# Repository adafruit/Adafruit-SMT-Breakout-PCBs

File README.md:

## Adafruit SMT Breakout PCBs
<a href="http://www.adafruit.com/products/1377"><br/>
Click here to purchase one from the Adafruit shop</a>

Beguiled by a fancy new chip that is only available in a strange pinout? These breakout PCBs will make your life much much easier and get you prototyping faster than ever.

All the basic SMT breakouts are here!

For more details, check out the product pages at

  * https://www.adafruit.com/products/1377 (48-pin)
  * https://www.adafruit.com/products/1162 (44-pin)
  * https://www.adafruit.com/products/1163 (32-pin)
  * https://www.adafruit.com/products/1208 (28-pin)
  * https://www.adafruit.com/products/1206 (20-pin)
  * https://www.adafruit.com/products/1207 (16-pin)
  * https://www.adafruit.com/products/1210 (14-pin)
  * https://www.adafruit.com/products/1211 (12-pin)
  * https://www.adafruit.com/products/1212 (8-pin)
  * https://www.adafruit.com/products/1230 (SOT & TO252 set)
  * https://www.adafruit.com/product/1762 (5050 LED)
  * https://www.adafruit.com/product/1863 (JST 2-PH w/switch)
  * https://www.adafruit.com/products/1862 (JST 2-PH)
  * https://www.adafruit.com/products/1868 (12mm coin)
  * https://www.adafruit.com/products/1867 (12mm coin w/switch)
  * https://www.adafruit.com/products/1870 (20mm coin)
  * https://www.adafruit.com/products/1871 (20mm coin w/switch)
  * https://www.adafruit.com/products/1833 (micro B)
  * https://www.adafruit.com/products/1764 (mini B)
  * https://www.adafruit.com/product/4984 (DVI)
  
PCB files for Adafruit SMT Basic Breakouts. The format is EagleCAD schematic and board layout

### License

Adafruit invests time and resources providing this open source design, please support Adafruit and open-source hardware by purchasing products from [Adafruit](https://www.adafruit.com)!

All text above must be included in any redistribution

Designed by Limor Fried/Ladyada for Adafruit Industries.
Creative Commons Attribution/Share-Alike, all text above must be included in any redistribution. 
See license.txt for additional information.

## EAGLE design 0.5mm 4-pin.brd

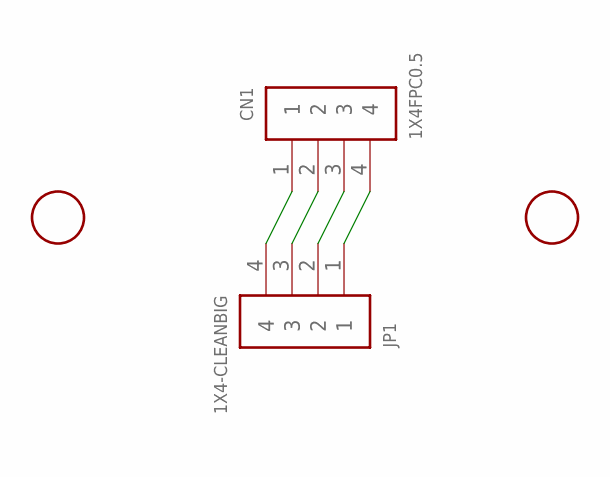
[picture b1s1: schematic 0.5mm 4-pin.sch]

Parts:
CN1: 1X4FPC0.5; FPC_0.5MM-4
JP1: 1X4-CLEANBIG; 1X04-CLEANBIG
U$2, U$3: FIDUCIAL; FIDUCIAL_1MM

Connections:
unnamed: CN1.4, JP1.1
unnamed: CN1.3, JP1.2
unnamed: CN1.2, JP1.3
unnamed: CN1.1, JP1.4

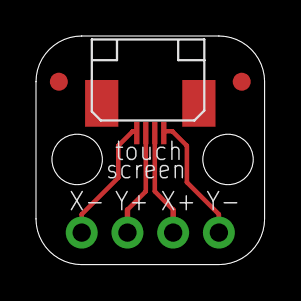
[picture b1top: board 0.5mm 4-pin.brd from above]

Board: 2 copper layers, 12.7 x 12.7 mm, 5 parts (1 on the bottom side), 4 nets.

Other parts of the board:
U$1: ADAFRUIT200MIL

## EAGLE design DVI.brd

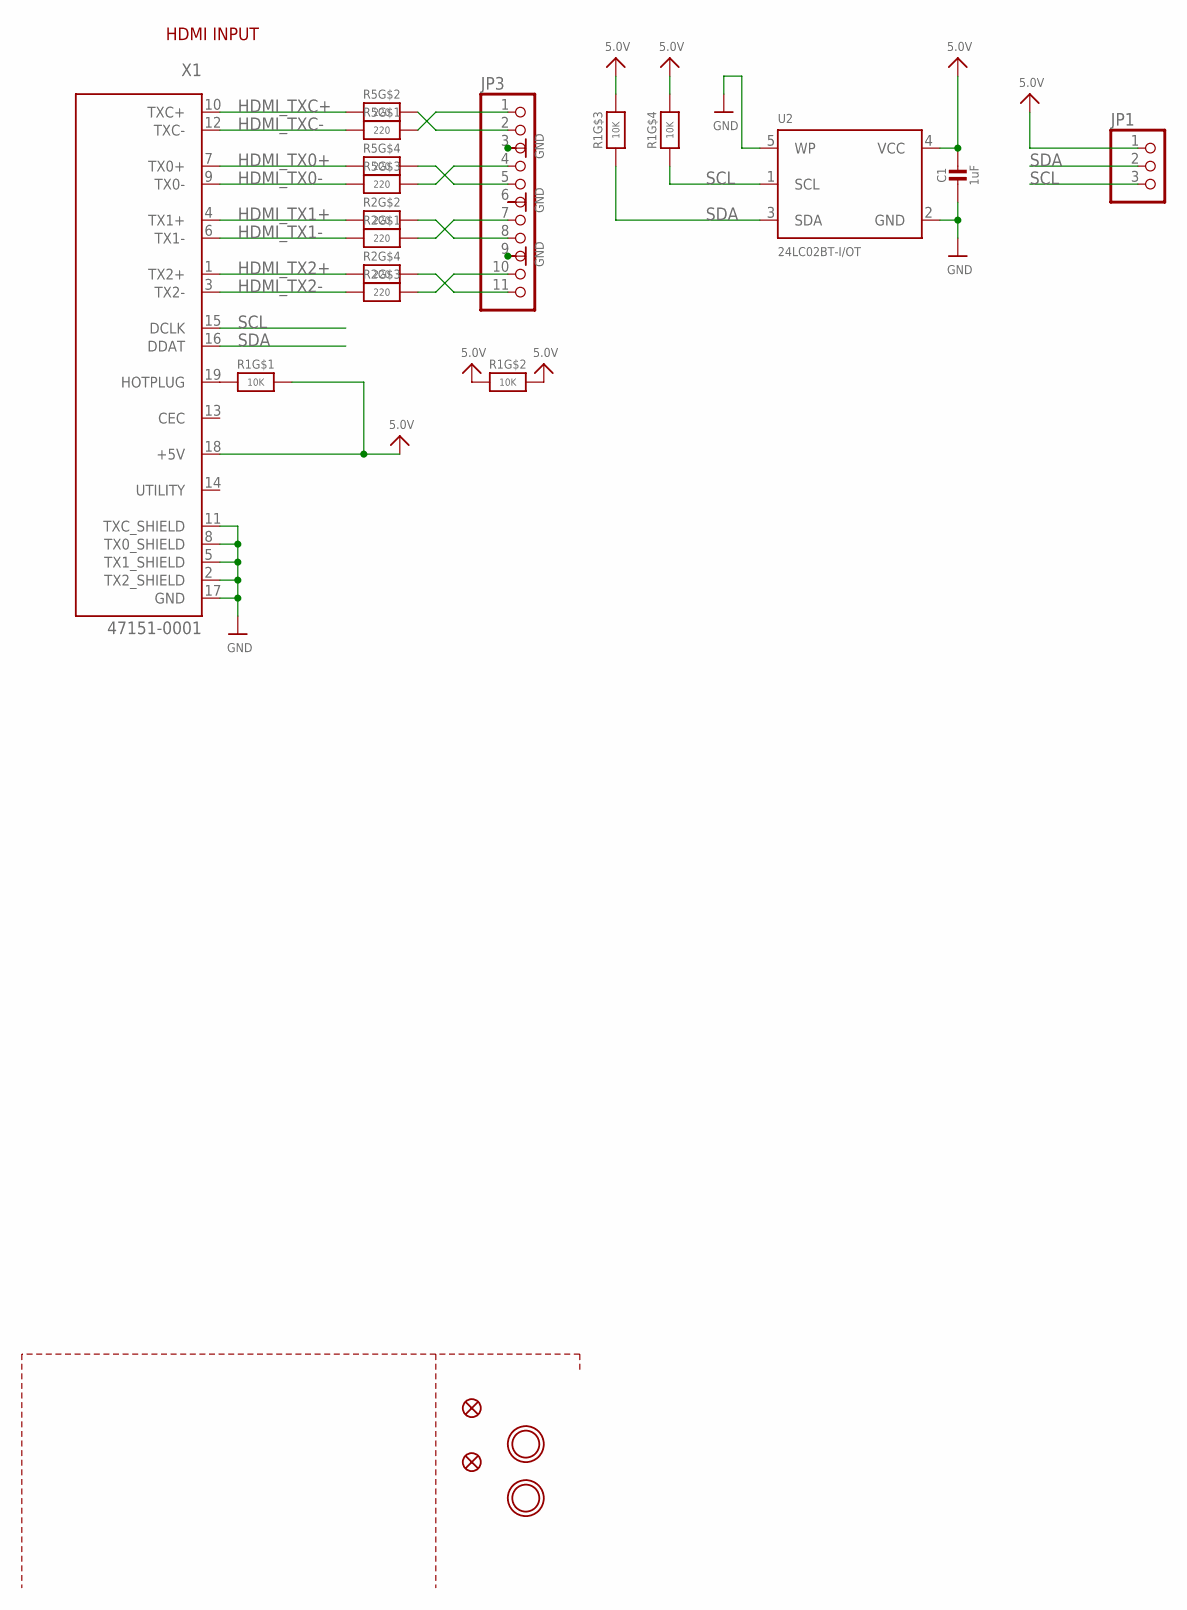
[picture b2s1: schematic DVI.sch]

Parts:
C1: 1uF; 0603-NO
FID1, FID2: FIDUCIAL_1MM
JP1: HEADER-1X3ROUND; 1X03_ROUND
JP3: HEADER-1X11; 1X11_ROUND
R1: 10K; RESPACK_4X0603
R2, R5: 220; RESPACK_4X0603
U2: 24LC02BT-I/OT; SOT23-5
U$32, U$33: MOUNTINGHOLE2.5; MOUNTINGHOLE_2.5_PLATED
X1: 47151-0001; HDMI_MOLEX_47151-0001

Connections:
5.0V: C1.1, JP1.1, R1.2 (1), R1.5 (2), R1.6 (2), R1.7 (2), R1.8 (2), U2.4 (VCC), X1.18 (+5V)
GND: C1.2, JP3.3, JP3.6, JP3.9, U2.2 (GND), U2.5 (WP), X1.2 (TX2_SHIELD), X1.5 (TX1_SHIELD), X1.8 (TX0_SHIELD), X1.11 (TXC_SHIELD), X1.17 (GND), X1.P$1 (GND), X1.P$2 (GND), X1.P$3 (GND), X1.P$4 (GND)
HDMI_TX0+: R5.4 (1), X1.7 (TX0+)
HDMI_TX0-: R5.3 (1), X1.9 (TX0-)
HDMI_TX1+: R2.2 (1), X1.4 (TX1+)
HDMI_TX1-: R2.1, X1.6 (TX1-)
HDMI_TX2+: R2.4 (1), X1.1 (TX2+)
HDMI_TX2-: R2.3 (1), X1.3 (TX2-)
HDMI_TXC+: R5.2 (1), X1.10 (TXC+)
HDMI_TXC-: R5.1, X1.12 (TXC-)
unnamed: R1.1, X1.19 (HOTPLUG)
SCL: JP1.3, R1.4 (1), U2.1 (SCL), X1.15 (DCLK)
SDA: JP1.2, R1.3 (1), U2.3 (SDA), X1.16 (DDAT)
TX0+: JP3.5, R5.5 (2)
TX0-: JP3.4, R5.6 (2)
TX1+: JP3.8, R2.7 (2)
TX1-: JP3.7, R2.8 (2)
TX2+: JP3.11, R2.5 (2)
TX2-: JP3.10, R2.6 (2)
TXC+: JP3.2, R5.7 (2)
TXC-: JP3.1, R5.8 (2)

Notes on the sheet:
HDMI INPUT

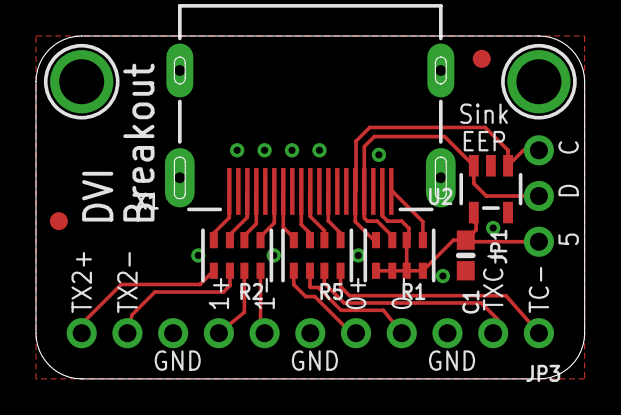
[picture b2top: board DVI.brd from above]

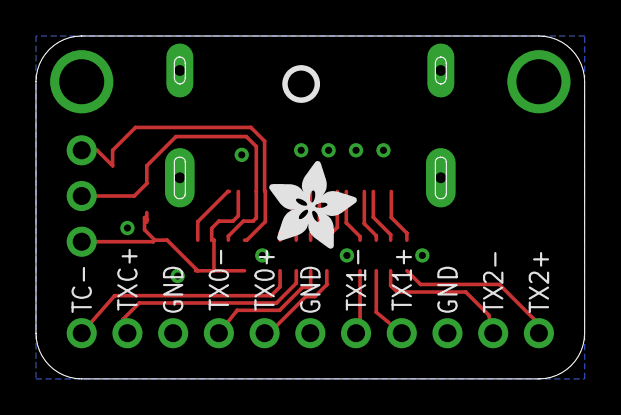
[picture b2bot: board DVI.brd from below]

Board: 2 copper layers, 30.5 x 19.1 mm, 14 parts (2 on the bottom side), 21 nets.

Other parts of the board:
U$6: ADAFRUIT_5MM
U$73: PCBFEAT-REV-040

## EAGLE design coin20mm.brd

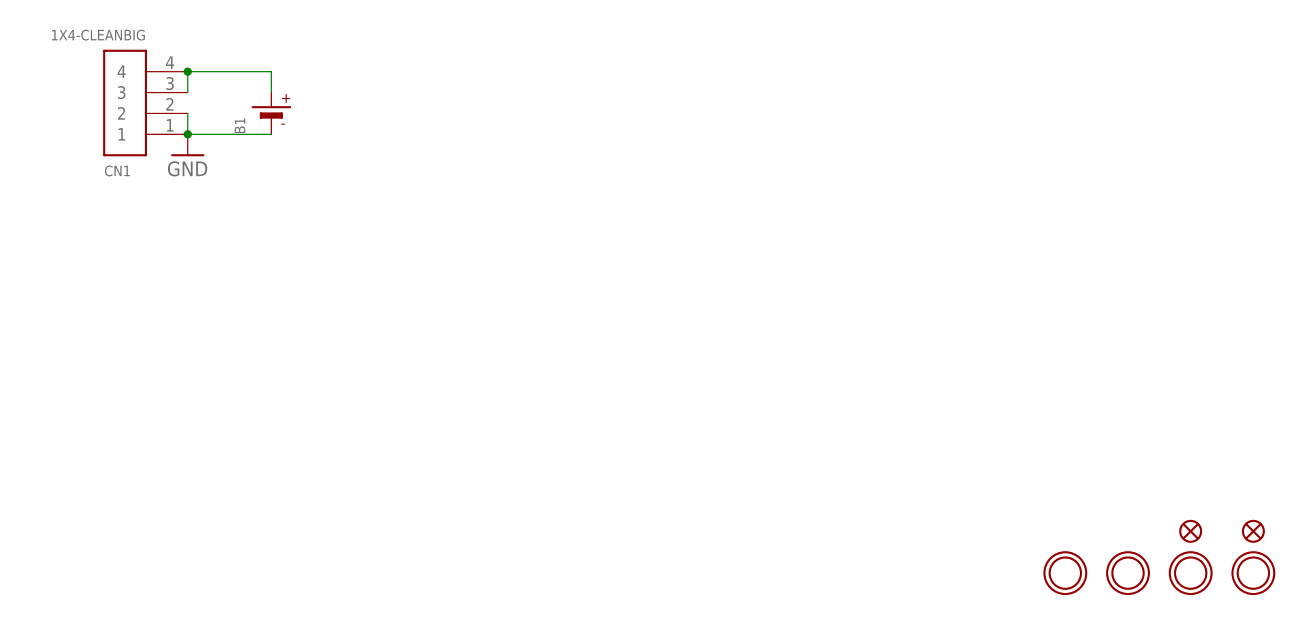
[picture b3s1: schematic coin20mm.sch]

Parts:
B1: BATTERYCR2032_BAT-HLD-001; CR2032_SMT_BAT-HLD-001
CN1: 1X4-CLEANBIG; 1X04-CLEANBIG
FID1, FID2: FIDUCIAL""; FIDUCIAL_1MM
U$1, U$2, U$3, U$5: MOUNTINGHOLE2.5; MOUNTINGHOLE_2.5_PLATED

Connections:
3V: B1.+$1 (+), B1.+$2 (+), CN1.3, CN1.4
GND: B1.-, CN1.1, CN1.2

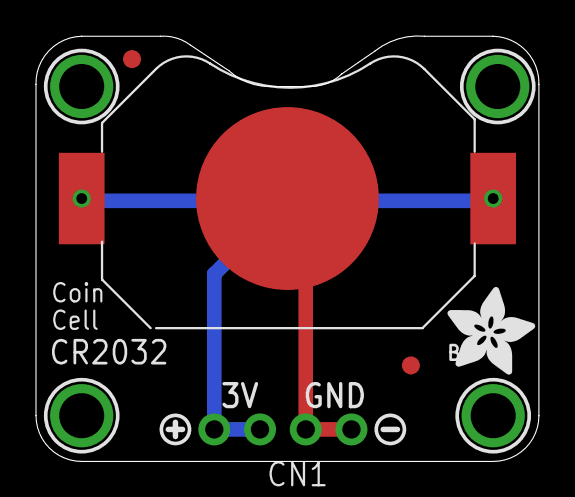
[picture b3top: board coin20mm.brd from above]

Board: 2 copper layers, 27.9 x 23.6 mm, 11 parts (0 on the bottom side), 2 nets.

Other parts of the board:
U$4: ADAFRUIT_5MM
U$6: SYMBOL_PLUS
U$7: SYMBOL_MINUS

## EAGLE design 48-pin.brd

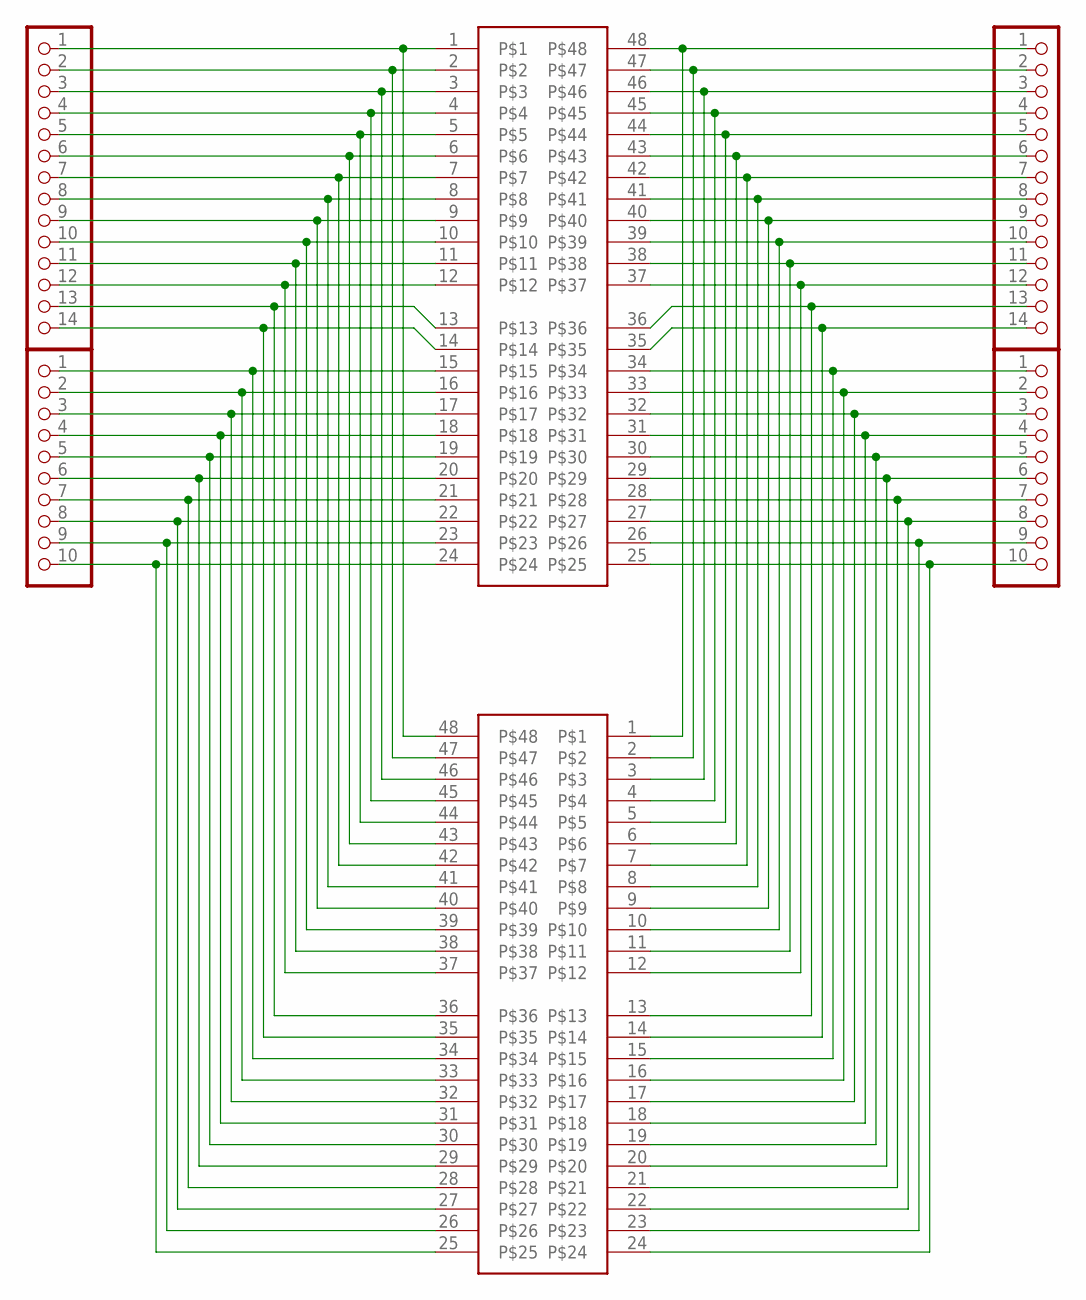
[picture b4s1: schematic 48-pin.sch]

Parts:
JP1, JP2: PADS-14
JP3, JP4: PADS-10
U$1: BREAKOUTS_48-PINTQFP; BREAKOUTS_TQFP48
U$2: BREAKOUTS_48-PINQFN; BREAKOUTS_QFN48

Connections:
.05: JP4.6, U$1.29, U$2.20
unnamed: JP1.1, U$1.1, U$2.48
unnamed: JP1.2, U$1.2, U$2.47
unnamed: JP1.3, U$1.3, U$2.46
unnamed: JP1.4, U$1.4, U$2.45
unnamed: JP1.5, U$1.5, U$2.44
unnamed: JP1.6, U$1.6, U$2.43
unnamed: JP1.7, U$1.7, U$2.42
unnamed: JP1.8, U$1.8, U$2.41
unnamed: JP1.9, U$1.9, U$2.40
unnamed: JP1.10, U$1.10, U$2.39
unnamed: JP1.11, U$1.11, U$2.38
unnamed: JP1.12, U$1.12, U$2.37
unnamed: JP3.1, U$1.15, U$2.34
unnamed: JP3.2, U$1.16, U$2.33
unnamed: JP3.3, U$1.17, U$2.32
unnamed: JP3.4, U$1.18, U$2.31
unnamed: JP3.5, U$1.19, U$2.30
unnamed: JP3.6, U$1.20, U$2.29
unnamed: JP3.7, U$1.21, U$2.28
unnamed: JP3.8, U$1.22, U$2.27
unnamed: JP3.9, U$1.23, U$2.26
unnamed: JP3.10, U$1.24, U$2.25
unnamed: JP2.1, U$1.48, U$2.1
unnamed: JP2.2, U$1.47, U$2.2
unnamed: JP2.3, U$1.46, U$2.3
unnamed: JP2.4, U$1.45, U$2.4
unnamed: JP2.5, U$1.44, U$2.5
unnamed: JP2.6, U$1.43, U$2.6
unnamed: JP2.7, U$1.42, U$2.7
unnamed: JP2.8, U$1.41, U$2.8
unnamed: JP2.10, U$1.39, U$2.10
unnamed: JP2.11, U$1.38, U$2.11
unnamed: JP2.12, U$1.37, U$2.12
unnamed: JP4.1, U$1.34, U$2.15
unnamed: JP4.2, U$1.33, U$2.16
unnamed: JP4.3, U$1.32, U$2.17
unnamed: JP4.4, U$1.31, U$2.18
unnamed: JP4.5, U$1.30, U$2.19
unnamed: JP4.7, U$1.28, U$2.21
unnamed: JP4.8, U$1.27, U$2.22
unnamed: JP4.9, U$1.26, U$2.23
unnamed: JP4.10, U$1.25, U$2.24
unnamed: JP1.14, U$1.14, U$2.35
unnamed: JP2.14, U$1.35, U$2.14
unnamed: JP2.13, U$1.36, U$2.13
unnamed: JP1.13, U$1.13, U$2.36
unnamed: JP2.9, U$1.40, U$2.9

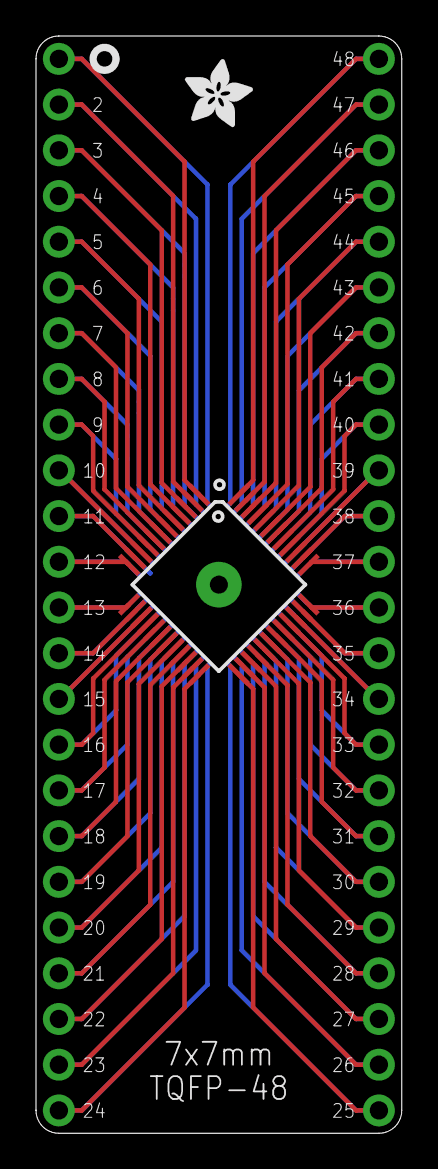
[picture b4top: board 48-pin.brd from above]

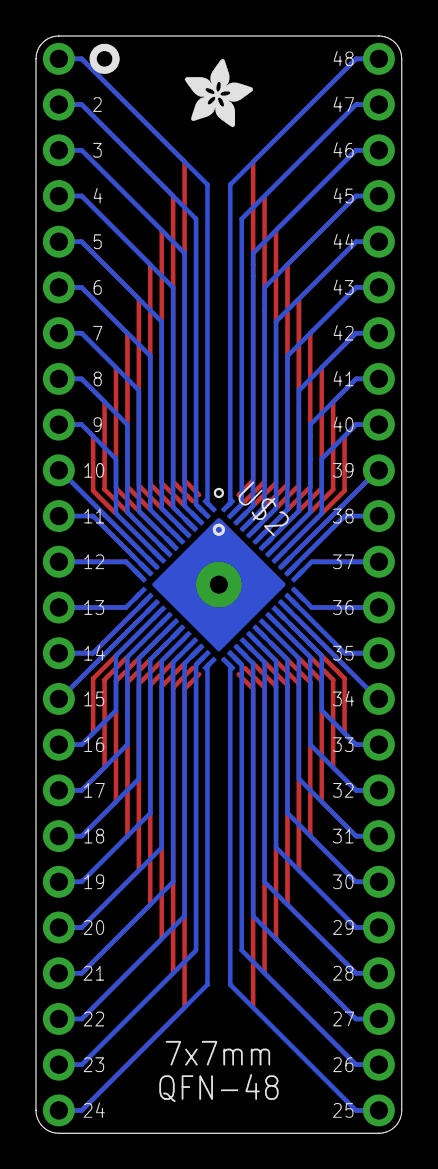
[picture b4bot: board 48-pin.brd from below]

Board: 2 copper layers, 20.3 x 61.0 mm, 8 parts (2 on the bottom side), 48 nets.

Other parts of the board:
U$3, U$4: ADAFRUIT_3.5MM

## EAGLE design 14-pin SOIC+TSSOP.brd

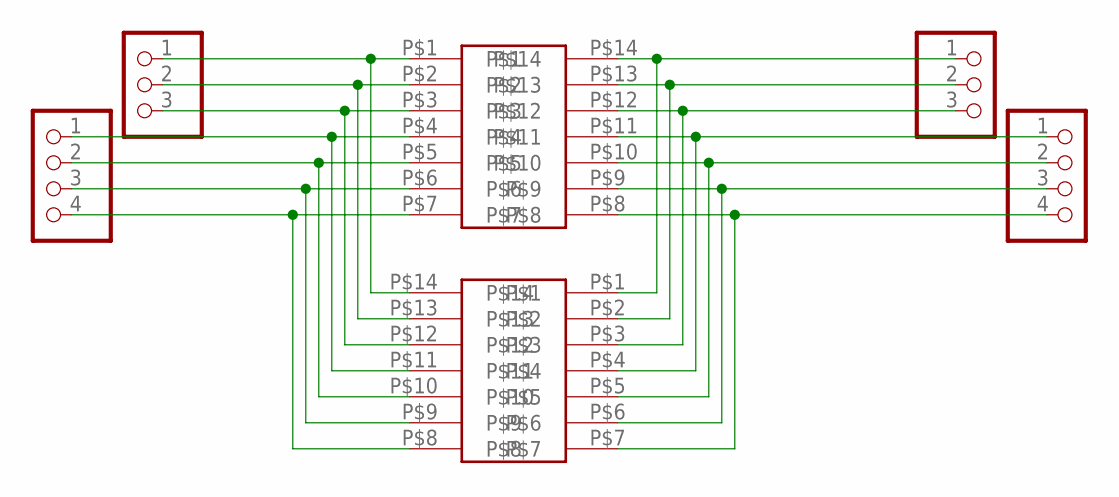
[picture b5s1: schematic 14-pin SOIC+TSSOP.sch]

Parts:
JP1, JP2: PADS-3
JP3, JP4: PADS-4
U$1: 14-PINSOIC-NW; SO14-NW
U$2: 14-PINTSSOP-NW; TSSOP14-NW

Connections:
unnamed: JP2.1, U$1.P$1, U$2.P$14
unnamed: JP2.2, U$1.P$2, U$2.P$13
unnamed: JP2.3, U$1.P$3, U$2.P$12
unnamed: JP4.1, U$1.P$4, U$2.P$11
unnamed: JP4.2, U$1.P$5, U$2.P$10
unnamed: JP4.3, U$1.P$6, U$2.P$9
unnamed: JP4.4, U$1.P$7, U$2.P$8
unnamed: JP1.1, U$1.P$14, U$2.P$1
unnamed: JP1.2, U$1.P$13, U$2.P$2
unnamed: JP1.3, U$1.P$12, U$2.P$3
unnamed: JP3.1, U$1.P$11, U$2.P$4
unnamed: JP3.2, U$1.P$10, U$2.P$5
unnamed: JP3.3, U$1.P$9, U$2.P$6
unnamed: JP3.4, U$1.P$8, U$2.P$7

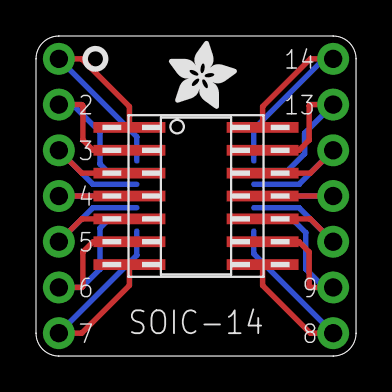
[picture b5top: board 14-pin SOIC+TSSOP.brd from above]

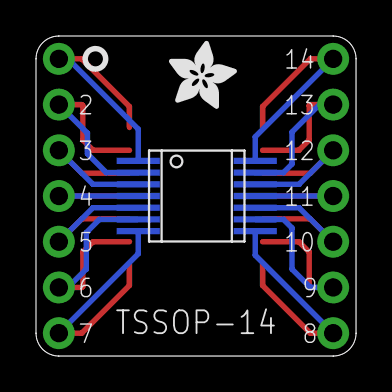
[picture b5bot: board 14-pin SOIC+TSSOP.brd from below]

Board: 2 copper layers, 17.8 x 17.8 mm, 8 parts (2 on the bottom side), 14 nets.

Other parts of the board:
U$3, U$4: ADAFRUIT_3.5MM

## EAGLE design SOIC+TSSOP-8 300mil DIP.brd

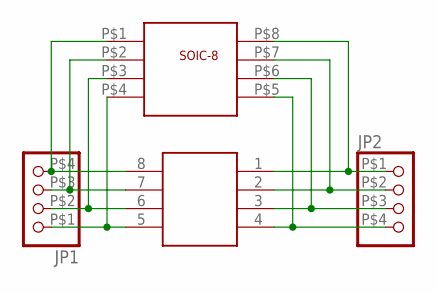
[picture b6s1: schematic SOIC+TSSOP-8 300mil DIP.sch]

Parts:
JP1, JP2: PINHD-1X4THIN; HEADER1X4
U$1: SO-8; SO-08NMW
U$2: TSSOP-8; TSSOP-8NM

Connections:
unnamed: JP1.P$4 (4), U$1.P$1, U$2.8
unnamed: JP1.P$3 (3), U$1.P$2, U$2.7
unnamed: JP1.P$2 (2), U$1.P$3, U$2.6
unnamed: JP1.P$1 (1), U$1.P$4, U$2.5
unnamed: JP2.P$4 (4), U$1.P$5, U$2.4
unnamed: JP2.P$3 (3), U$1.P$6, U$2.3
unnamed: JP2.P$2 (2), U$1.P$7, U$2.2
unnamed: JP2.P$1 (1), U$1.P$8, U$2.1

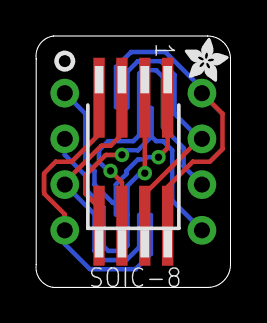
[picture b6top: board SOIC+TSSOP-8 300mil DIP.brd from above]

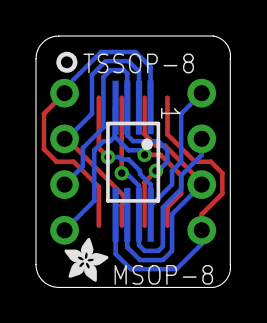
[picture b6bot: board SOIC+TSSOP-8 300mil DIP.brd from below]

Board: 2 copper layers, 10.8 x 14.0 mm, 6 parts (2 on the bottom side), 8 nets.

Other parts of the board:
U$3, U$4: ADAFRUIT_2.5MM

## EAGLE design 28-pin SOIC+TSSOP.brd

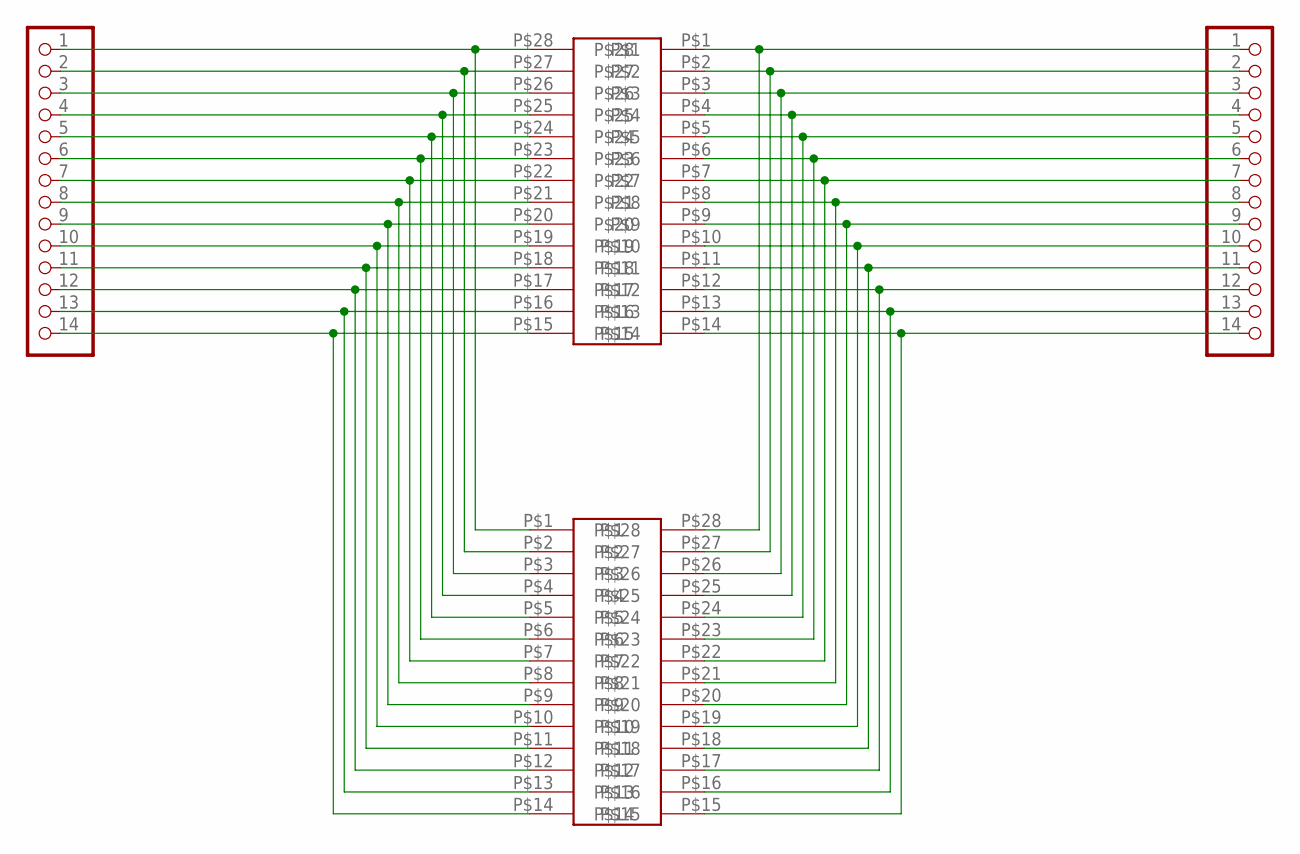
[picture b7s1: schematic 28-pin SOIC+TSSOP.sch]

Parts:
JP1, JP2: PADS-14
U$1: 28-PINSOIC-NW; SO28-NW
U$2: 28-PINTSSOP-NW; TSSOP28-NW

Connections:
unnamed: JP1.1, U$1.P$1, U$2.P$28
unnamed: JP1.2, U$1.P$2, U$2.P$27
unnamed: JP1.3, U$1.P$3, U$2.P$26
unnamed: JP1.4, U$1.P$4, U$2.P$25
unnamed: JP1.5, U$1.P$5, U$2.P$24
unnamed: JP1.6, U$1.P$6, U$2.P$23
unnamed: JP1.7, U$1.P$7, U$2.P$22
unnamed: JP1.8, U$1.P$8, U$2.P$21
unnamed: JP1.9, U$1.P$9, U$2.P$20
unnamed: JP1.10, U$1.P$10, U$2.P$19
unnamed: JP1.11, U$1.P$11, U$2.P$18
unnamed: JP1.12, U$1.P$12, U$2.P$17
unnamed: JP1.14, U$1.P$14, U$2.P$15
unnamed: JP2.1, U$1.P$28, U$2.P$1
unnamed: JP2.2, U$1.P$27, U$2.P$2
unnamed: JP2.3, U$1.P$26, U$2.P$3
unnamed: JP2.4, U$1.P$25, U$2.P$4
unnamed: JP2.5, U$1.P$24, U$2.P$5
unnamed: JP2.6, U$1.P$23, U$2.P$6
unnamed: JP2.7, U$1.P$22, U$2.P$7
unnamed: JP2.8, U$1.P$21, U$2.P$8
unnamed: JP2.9, U$1.P$20, U$2.P$9
unnamed: JP2.10, U$1.P$19, U$2.P$10
unnamed: JP2.11, U$1.P$18, U$2.P$11
unnamed: JP2.12, U$1.P$17, U$2.P$12
unnamed: JP2.13, U$1.P$16, U$2.P$13
unnamed: JP2.14, U$1.P$15, U$2.P$14
unnamed: JP1.13, U$1.P$13, U$2.P$16

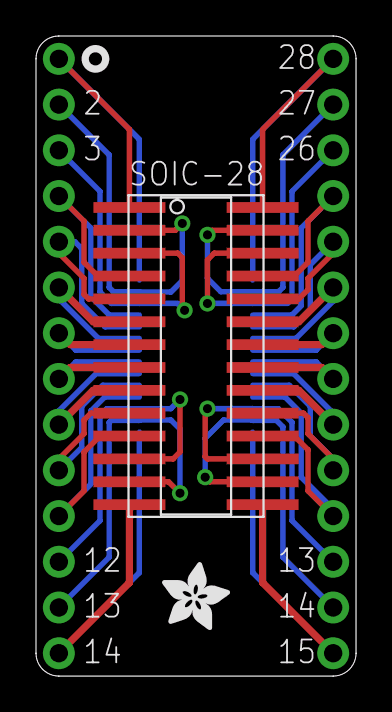
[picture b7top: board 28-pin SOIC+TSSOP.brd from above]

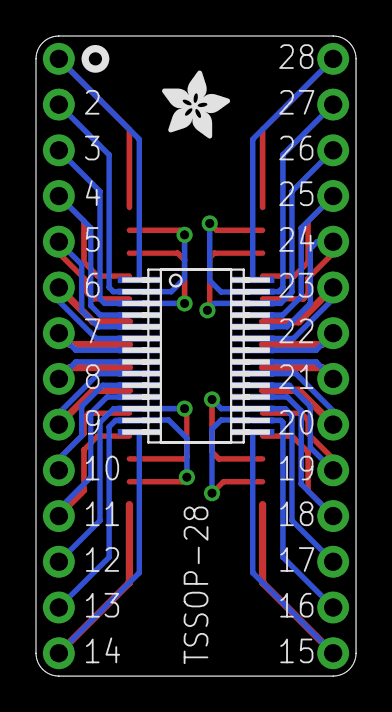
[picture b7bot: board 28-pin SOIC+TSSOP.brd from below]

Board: 2 copper layers, 17.8 x 35.6 mm, 6 parts (2 on the bottom side), 28 nets.

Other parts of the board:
U$3, U$4: ADAFRUIT_3.5MM

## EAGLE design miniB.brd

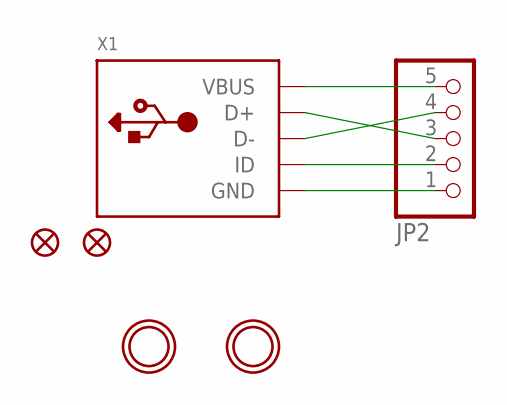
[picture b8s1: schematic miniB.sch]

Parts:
FID1, FID2: FIDUCIAL""; FIDUCIAL_1MM
JP2: HEADER-1X570MIL; 1X05_ROUND_70
U$1, U$2: MOUNTINGHOLE2.5; MOUNTINGHOLE_2.5_PLATED
X1: USBMINIBLARGE; USB-MINIB_LARGER

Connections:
D+: JP2.3, X1.D+
D-: JP2.4, X1.D-
GND: JP2.1, X1.GND, X1.GND1 (GND), X1.GND2 (GND), X1.GND3 (GND), X1.GND4 (GND)
ID: JP2.2, X1.ID
VBUS: JP2.5, X1.VBUS

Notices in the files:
parts and their libraries:
microbuilder: This work is placed in the public domain, and may be freely used for commercial and non-commercial work with the following conditions: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
